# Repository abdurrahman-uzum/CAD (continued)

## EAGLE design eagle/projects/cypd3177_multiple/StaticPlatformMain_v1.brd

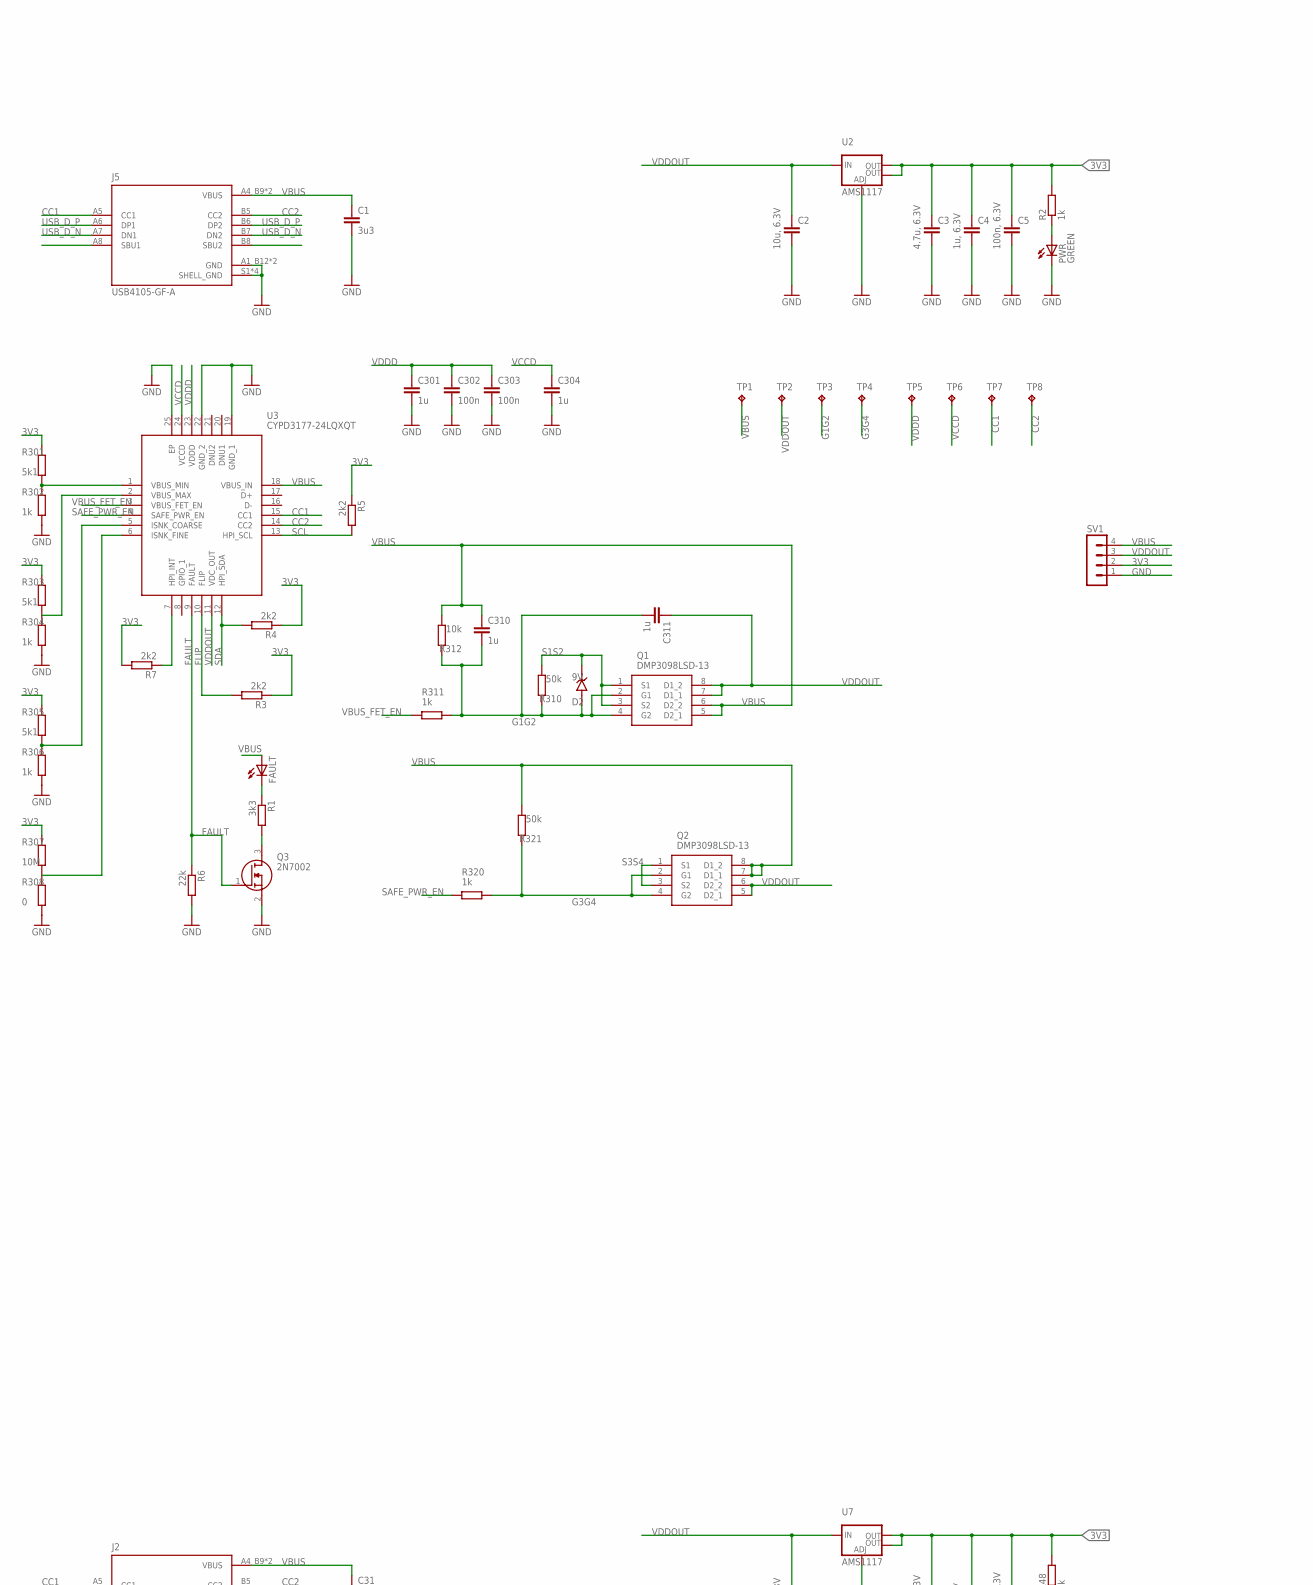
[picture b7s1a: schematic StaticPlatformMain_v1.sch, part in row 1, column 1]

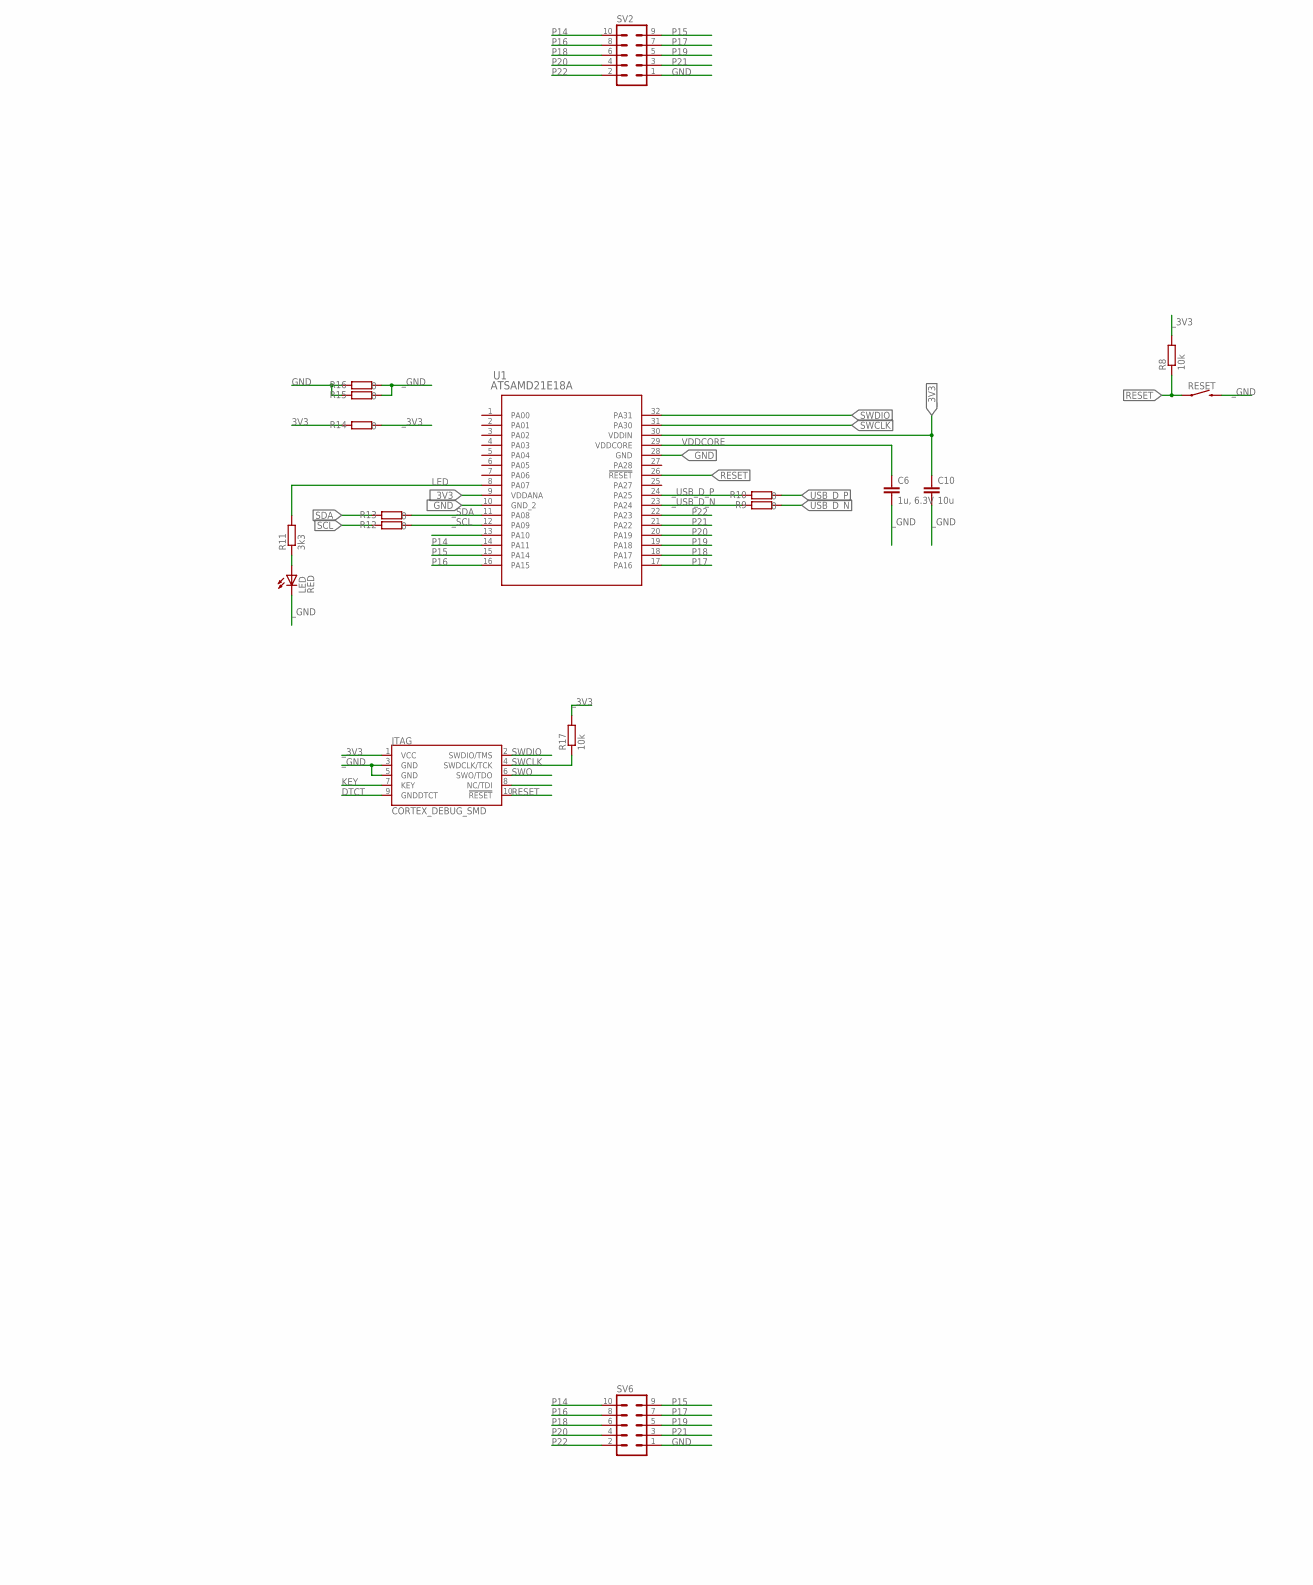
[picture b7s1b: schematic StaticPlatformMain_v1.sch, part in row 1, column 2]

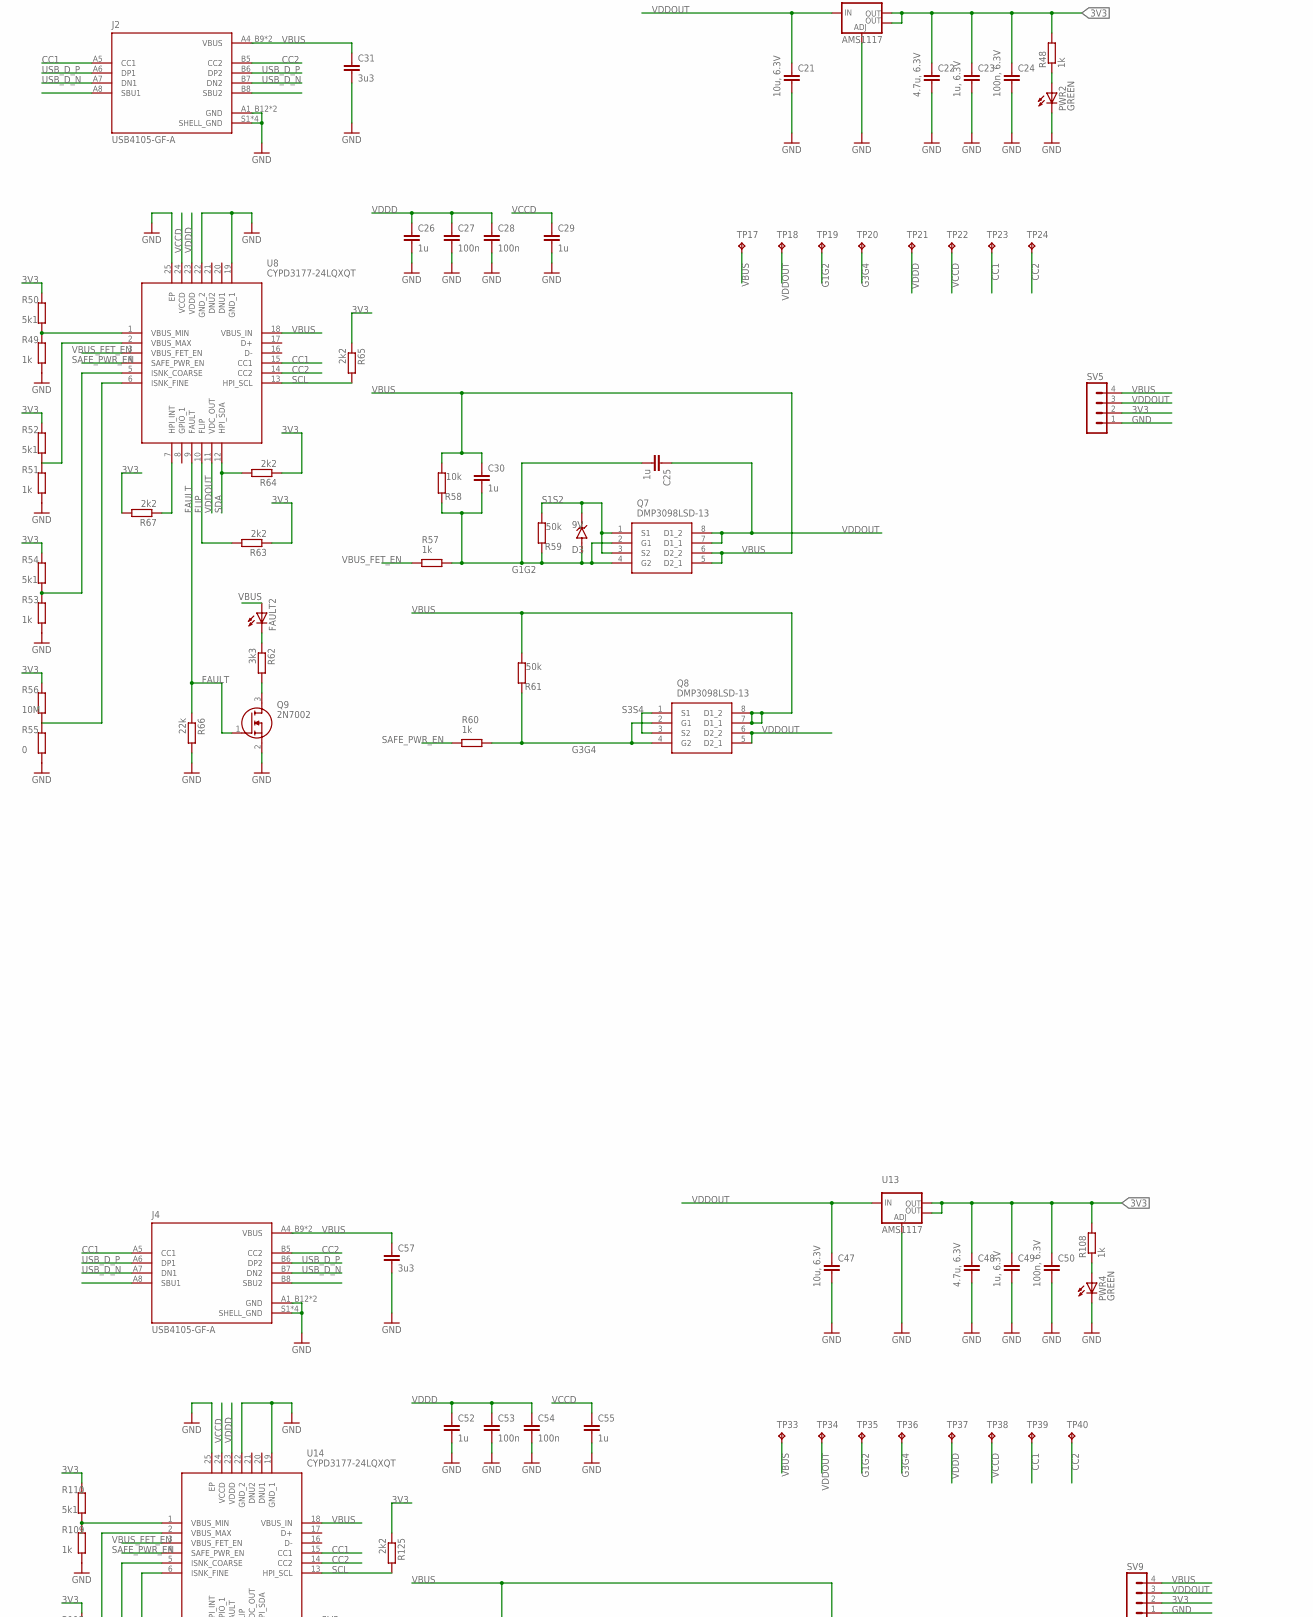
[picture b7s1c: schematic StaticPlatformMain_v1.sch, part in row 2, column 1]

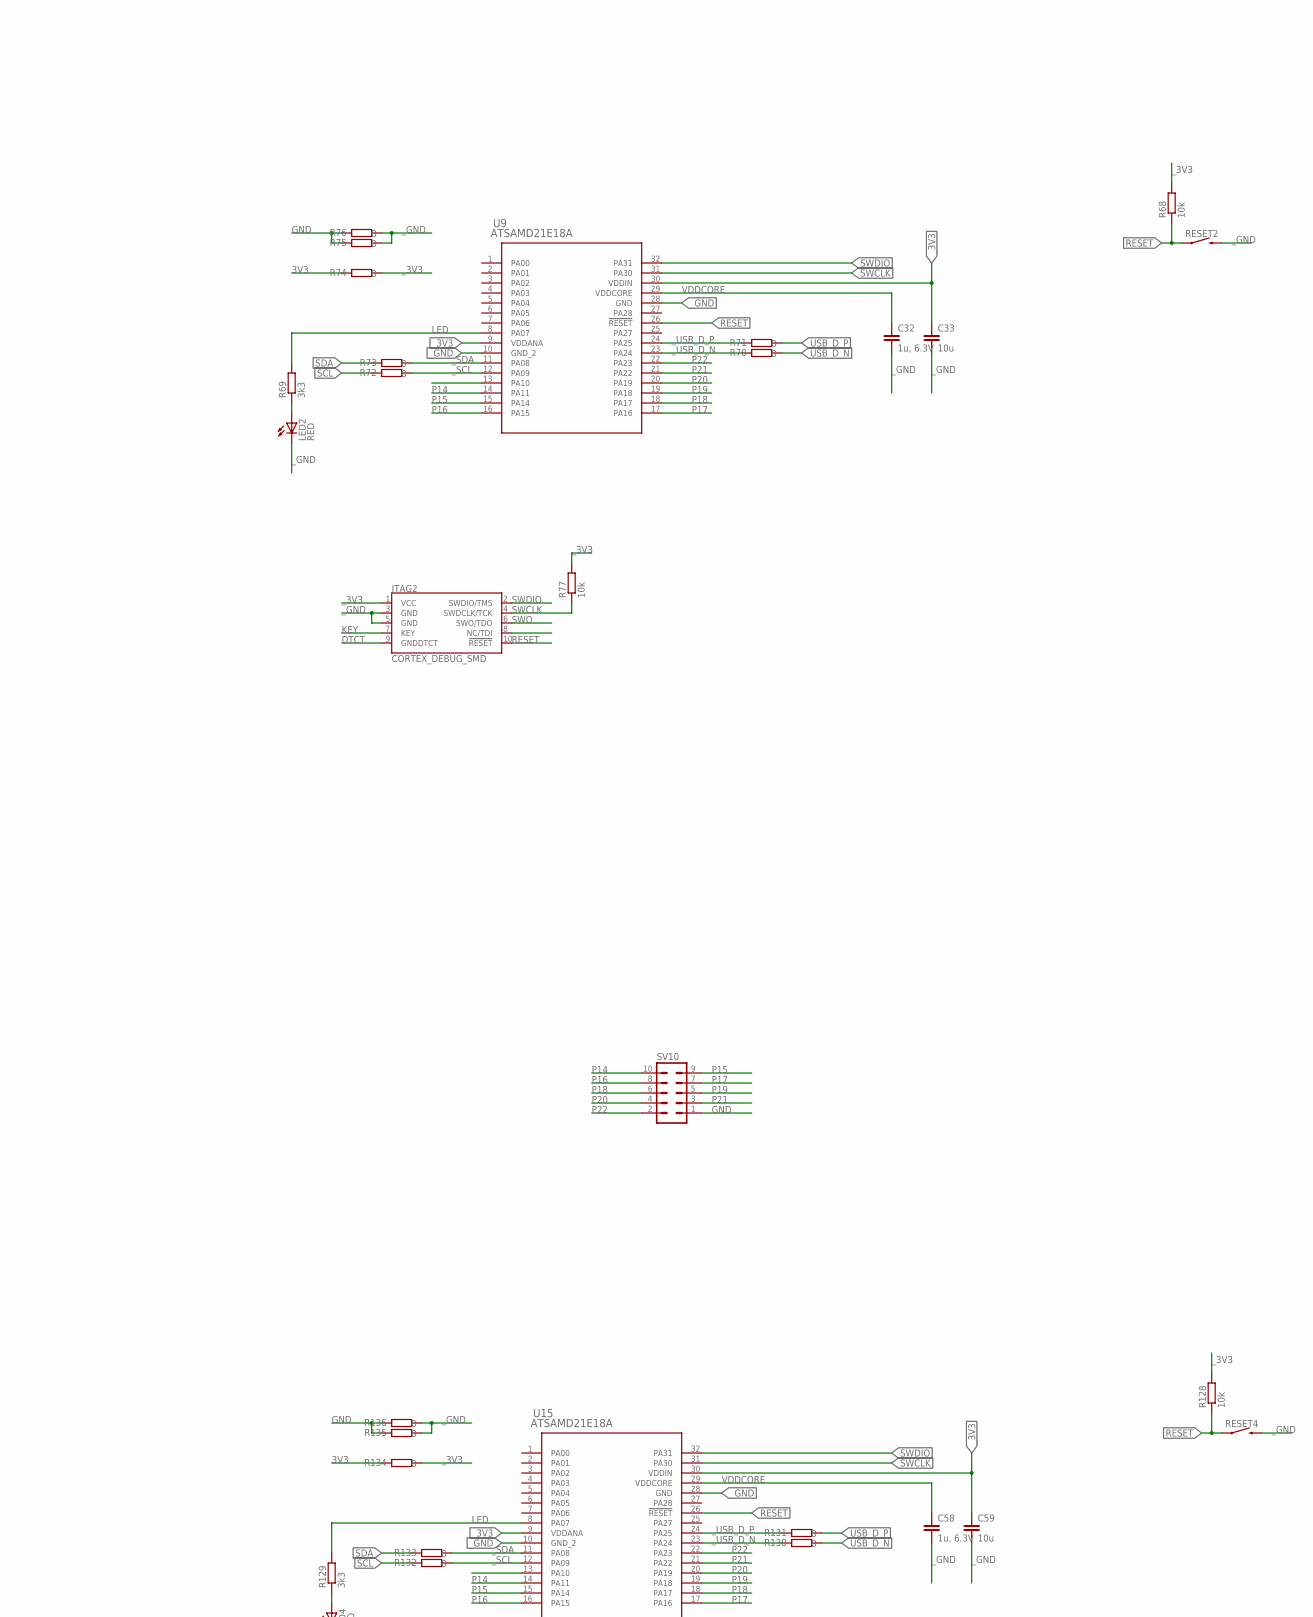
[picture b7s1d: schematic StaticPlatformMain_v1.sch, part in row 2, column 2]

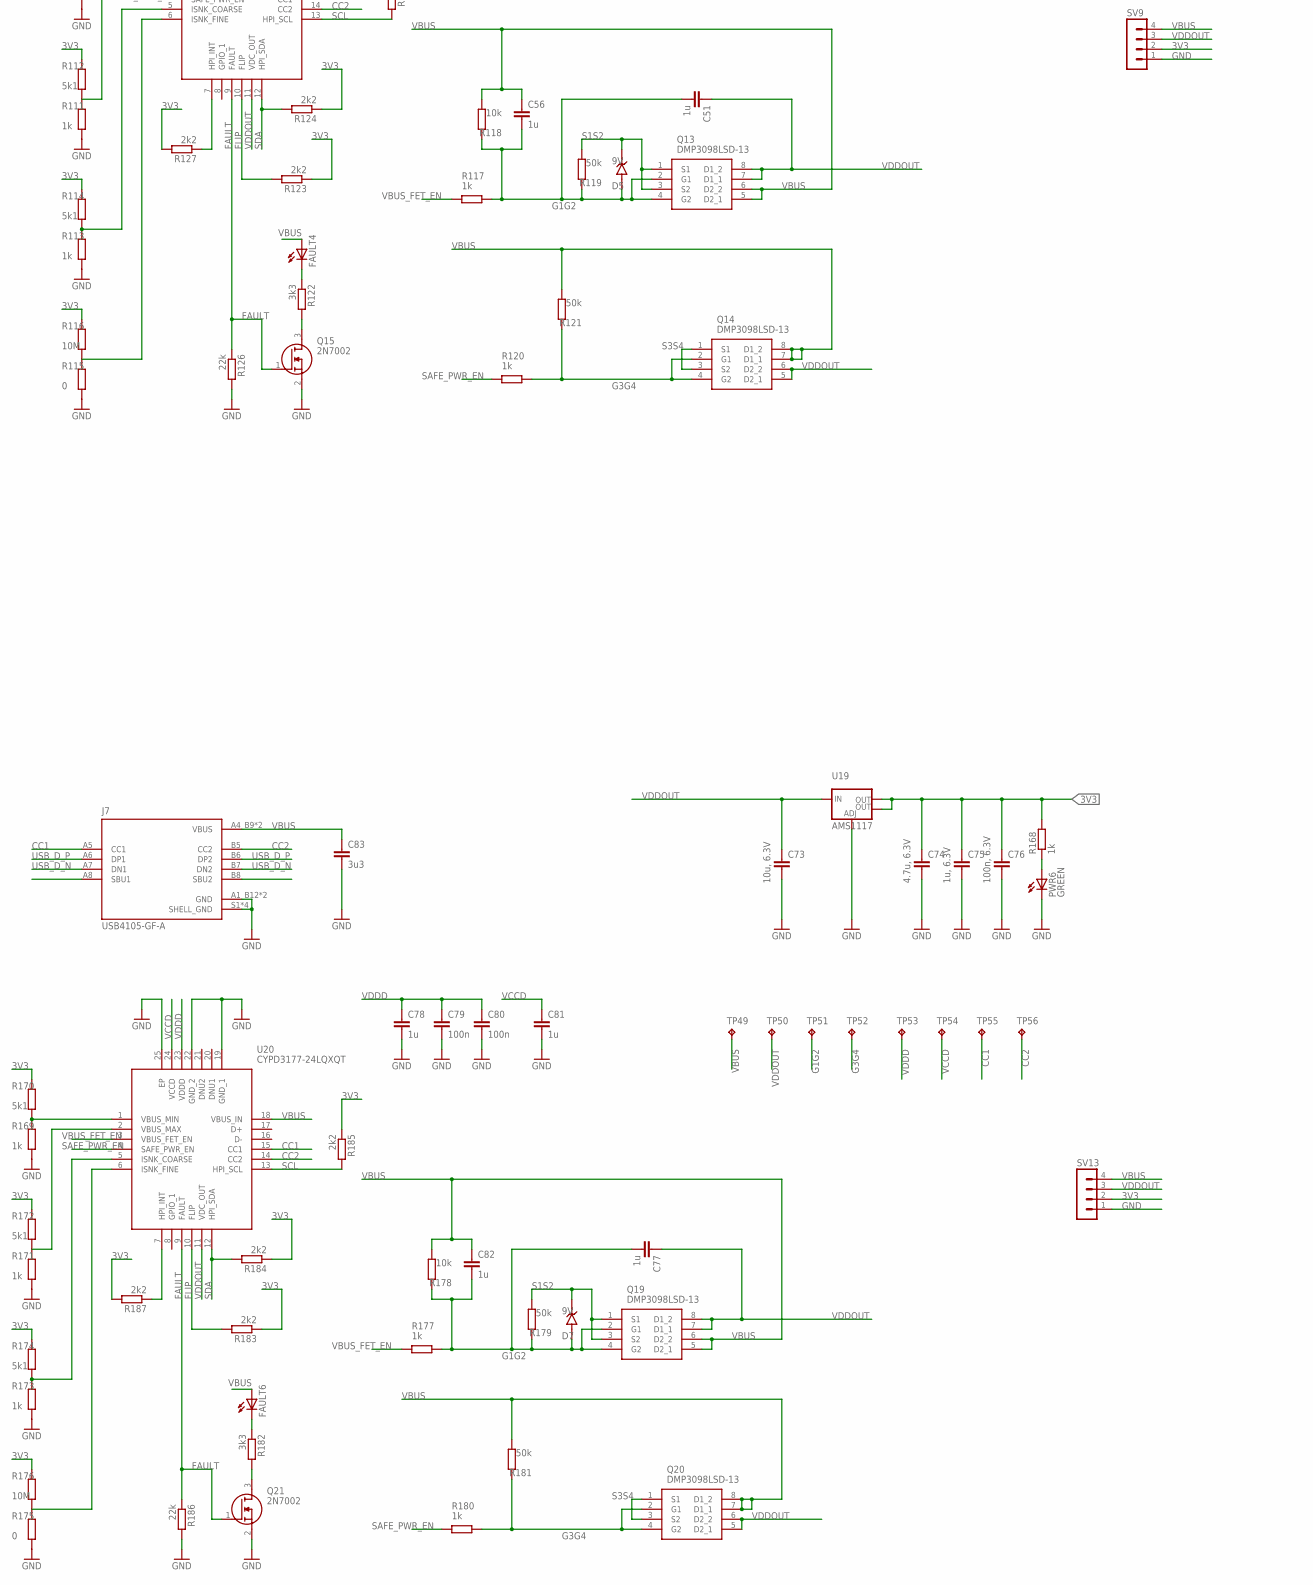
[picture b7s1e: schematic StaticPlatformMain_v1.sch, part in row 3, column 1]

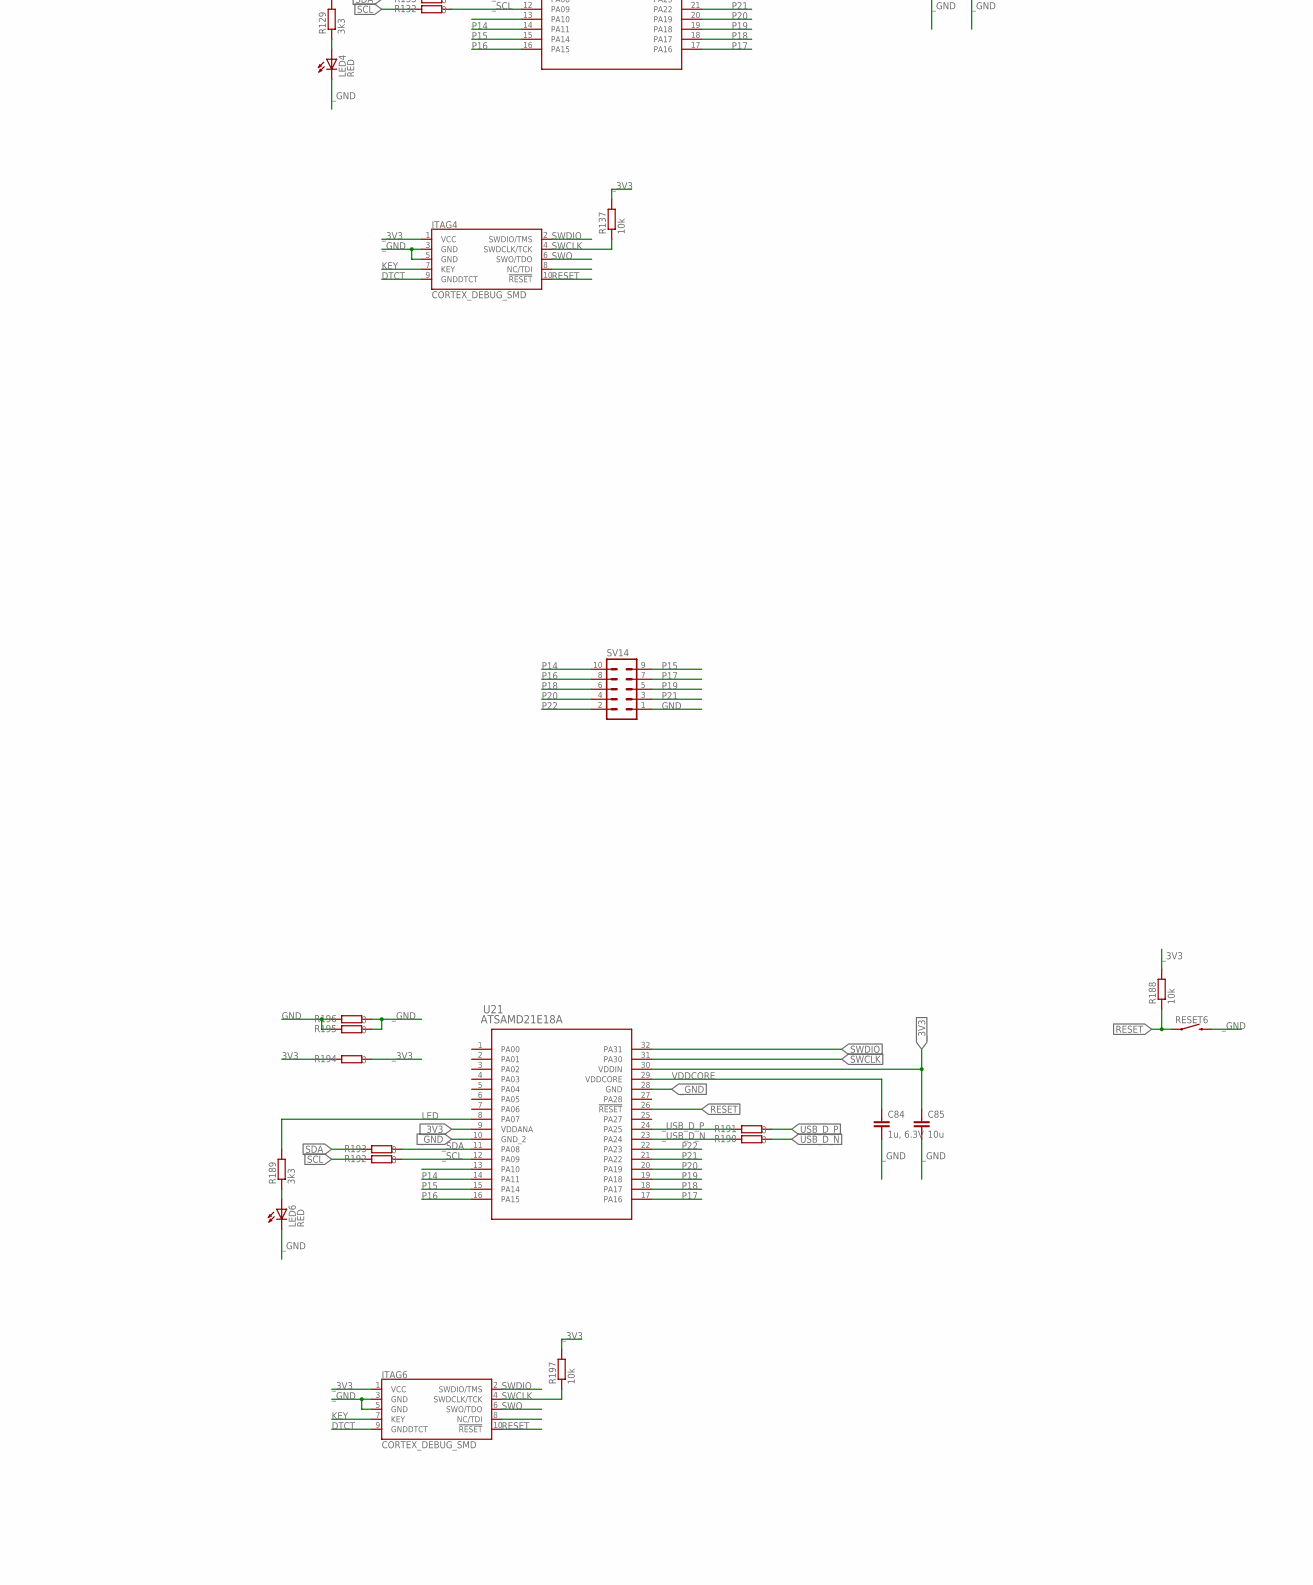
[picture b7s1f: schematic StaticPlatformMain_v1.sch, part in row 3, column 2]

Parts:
C1, C31, C57, C83: 3u3; C0805K
C2, C21, C47, C73: 10u, 6.3V; C0805K
C3, C22, C48, C74: 4.7u, 6.3V; C0805K
C4, C23, C49, C75: 1u, 6.3V; C0805K
C5, C24, C50, C76: 100n, 6.3V; C0805K
C6, C32, C58, C84: 1u, 6.3V; C0805
C10, C33, C59, C85: 10u; C0805
C25, C26, C29, C30, C51, C52, C55, C56, C77, C78, C81, C82, C301, C304, C310, C311: 1u; C0805K
C27, C28, C53, C54, C79, C80, C302, C303: 100n; C0805K
D2, D3, D5, D7: 9V; DIOMELF3515N
FAULT, FAULT2, FAULT4, FAULT6: GREEN; CHIPLED_0805
J2, J4, J5, J7: USB4105-GF-A; GCT_USB4105-GF-A
JTAG, JTAG2, JTAG4, JTAG6: CORTEX_DEBUG_SMD; SAMTECH_FTSH-105-01
LED, LED2, LED4, LED6: RED; CHIPLED_0805
PWR, PWR2, PWR4, PWR6: GREEN; CHIPLED_0805
Q1, Q2, Q7, Q8, Q13, Q14, Q19, Q20: DMP3098LSD-13; SOIC127P600X175-8N
Q3, Q9, Q15, Q21: 2N7002; SOT96P240X120-3N
R1, R11, R62, R69, R122, R129, R182, R189: 3k3; R0805
R2, R48, R49, R51, R53, R57, R60, R108, R109, R111, R113, R117, R120, R168, R169, R171, R173, R177, R180, R302, R304, R306, R311, R320: 1k; R0805
R3, R4, R5, R7, R63, R64, R65, R67, R123, R124, R125, R127, R183, R184, R185, R187: 2k2; R0805
R6, R66, R126, R186: 22k; R0805
R8, R17, R58, R68, R77, R118, R128, R137, R178, R188, R197, R312: 10k; R0805
R9, R10, R12, R13, R14, R15, R16, R55, R70, R71, R72, R73, R74, R75, R76, R115, R130, R131, R132, R133, R134, R135, R136, R175, R190, R191, R192, R193, R194, R195, R196, R308: 0; R0805
R50, R52, R54, R110, R112, R114, R170, R172, R174, R301, R303, R305: 5k1; R0805
R56, R116, R176, R307: 10M; R0805
R59, R61, R119, R121, R179, R181, R310, R321: 50k; R0805
RESET, RESET2, RESET4, RESET6: MOMENTARY-SWITCH-SPST-SMD-6.0X3.5MM; TACTILE_SWITCH_SMD_6.0X3.5MM
SV1, SV5, SV9, SV13: MA04-1
SV2, SV6, SV10, SV14: MA05-2
TP1, TP2, TP3, TP4, TP5, TP6, TP7, TP8, TP17, TP18, TP19, TP20, TP21, TP22, TP23, TP24, TP33, TP34, TP35, TP36, TP37, TP38, TP39, TP40, TP49, TP50, TP51, TP52, TP53, TP54, TP55, TP56: TPTP18R; TP18R
U1, U9, U15, U21: ATSAMD21E18A; TQFP32_MC_MCH-M
U2, U7, U13, U19: AMS1117; SOT223
U3, U8, U14, U20: CYPD3177-24LQXQT; QFN50P400X400X60-25N

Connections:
3V3: C3.1, C4.1, C5.1, C22.1, C23.1, C24.1, C48.1, C49.1, C50.1, C74.1, C75.1, C76.1, R2.2, R3.1, R4.1, R5.1, R7.2, R14.2, R48.2, R50.2, R52.2, R54.2, R56.2, R63.1, R64.1, R65.1, R67.2, R74.2, R108.2, R110.2, R112.2, R114.2, R116.2, R123.1, R124.1, R125.1, R127.2, R134.2, R168.2, R170.2, R172.2, R174.2, R176.2, R183.1, R184.1, R185.1, R187.2, R194.2, R301.2, R303.2, R305.2, R307.2, SV1.2, SV5.2, SV9.2, SV13.2, U2.2 (OUT), U2.4 (OUT), U7.2 (OUT), U7.4 (OUT), U13.2 (OUT), U13.4 (OUT), U19.2 (OUT), U19.4 (OUT)
CC1: J2.A5 (CC1), J4.A5 (CC1), J5.A5 (CC1), J7.A5 (CC1), TP7.TP, TP23.TP, TP39.TP, TP55.TP, U3.15 (CC1), U8.15 (CC1), U14.15 (CC1), U20.15 (CC1)
CC2: J2.B5 (CC2), J4.B5 (CC2), J5.B5 (CC2), J7.B5 (CC2), TP8.TP, TP24.TP, TP40.TP, TP56.TP, U3.14 (CC2), U8.14 (CC2), U14.14 (CC2), U20.14 (CC2)
DTCT: JTAG.9 (GNDDTCT), JTAG2.9 (GNDDTCT), JTAG4.9 (GNDDTCT), JTAG6.9 (GNDDTCT)
FAULT: Q3.1 (G), Q9.1 (G), Q15.1 (G), Q21.1 (G), R6.1, R66.1, R126.1, R186.1, U3.9 (FAULT), U8.9 (FAULT), U14.9 (FAULT), U20.9 (FAULT)
FLIP: R3.2, R63.2, R123.2, R183.2, U3.10 (FLIP), U8.10 (FLIP), U14.10 (FLIP), U20.10 (FLIP)
G1G2: C25.2, C30.2, C51.2, C56.2, C77.2, C82.2, C310.2, C311.2, D2.A, D3.A, D5.A, D7.A, Q1.2 (G1), Q1.4 (G2), Q7.2 (G1), Q7.4 (G2), Q13.2 (G1), Q13.4 (G2), Q19.2 (G1), Q19.4 (G2), R57.1, R58.2, R59.2, R117.1, R118.2, R119.2, R177.1, R178.2, R179.2, R310.2, R311.1, R312.2, TP3.TP, TP19.TP, TP35.TP, TP51.TP
G3G4: Q2.2 (G1), Q2.4 (G2), Q8.2 (G1), Q8.4 (G2), Q14.2 (G1), Q14.4 (G2), Q20.2 (G1), Q20.4 (G2), R60.1, R61.2, R120.1, R121.2, R180.1, R181.2, R320.1, R321.2, TP4.TP, TP20.TP, TP36.TP, TP52.TP
GND: C1.2, C2.2, C3.2, C4.2, C5.2, C21.2, C22.2, C23.2, C24.2, C26.2, C27.2, C28.2, C29.2, C31.2, C47.2, C48.2, C49.2, C50.2, C52.2, C53.2, C54.2, C55.2, C57.2, C73.2, C74.2, C75.2, C76.2, C78.2, C79.2, C80.2, C81.2, C83.2, C301.2, C302.2, C303.2, C304.2, J2.A1_B12 (GND), J2.B1_A12 (GND), J2.S1 (SHELL_GND), J2.S2 (SHELL_GND), J2.S3 (SHELL_GND), J2.S4 (SHELL_GND), J4.A1_B12 (GND), J4.B1_A12 (GND), J4.S1 (SHELL_GND), J4.S2 (SHELL_GND), J4.S3 (SHELL_GND), J4.S4 (SHELL_GND), J5.A1_B12 (GND), J5.B1_A12 (GND), J5.S1 (SHELL_GND), J5.S2 (SHELL_GND), J5.S3 (SHELL_GND), J5.S4 (SHELL_GND), J7.A1_B12 (GND), J7.B1_A12 (GND), J7.S1 (SHELL_GND), J7.S2 (SHELL_GND), J7.S3 (SHELL_GND), J7.S4 (SHELL_GND), PWR.C, PWR2.C, PWR4.C, PWR6.C, Q3.2 (S), Q9.2 (S), Q15.2 (S), Q21.2 (S), R6.2, R15.2, R16.2, R49.1, R51.1, R53.1, R55.1, R66.2, R75.2, R76.2, R109.1, R111.1, R113.1, R115.1, R126.2, R135.2, R136.2, R169.1, R171.1, R173.1, R175.1, R186.2, R195.2, R196.2, R302.1, R304.1, R306.1, R308.1, SV1.1, SV2.1, SV5.1, SV6.1, SV9.1, SV10.1, SV13.1, SV14.1, U2.1 (ADJ), U3.19 (GND_1), U3.22 (GND_2), U3.25 (EP), U7.1 (ADJ), U8.19 (GND_1), U8.22 (GND_2), U8.25 (EP), U13.1 (ADJ), U14.19 (GND_1), U14.22 (GND_2), U14.25 (EP), U19.1 (ADJ), U20.19 (GND_1), U20.22 (GND_2), U20.25 (EP)
KEY: JTAG.7 (KEY), JTAG2.7 (KEY), JTAG4.7 (KEY), JTAG6.7 (KEY)
LED: R11.2, R69.2, R129.2, R189.2, U1.8 (PA07), U9.8 (PA07), U15.8 (PA07), U21.8 (PA07)
LED_GP: LED.A, R11.1
LED_GP2: LED2.A, R69.1
LED_GP4: LED4.A, R129.1
LED_GP6: LED6.A, R189.1
LED_PWR: PWR.A, R2.1
LED_PWR2: PWR2.A, R48.1
LED_PWR4: PWR4.A, R108.1
LED_PWR6: PWR6.A, R168.1
unnamed: FAULT.C, R1.1
unnamed: R7.1, U3.7 (HPI_INT)
unnamed: R301.1, R302.2, U3.1 (VBUS_MIN)
unnamed: R303.1, R304.2, U3.2 (VBUS_MAX)
unnamed: R305.1, R306.2, U3.5 (ISNK_COARSE)
unnamed: Q3.3 (D), R1.2
unnamed: R307.1, R308.2, U3.6 (ISNK_FINE)
unnamed: R49.2, R50.1, U8.1 (VBUS_MIN)
unnamed: R51.2, R52.1, U8.2 (VBUS_MAX)
unnamed: R53.2, R54.1, U8.5 (ISNK_COARSE)
unnamed: R55.2, R56.1, U8.6 (ISNK_FINE)
unnamed: FAULT2.C, R62.1
unnamed: Q9.3 (D), R62.2
unnamed: R67.1, U8.7 (HPI_INT)
unnamed: R109.2, R110.1, U14.1 (VBUS_MIN)
unnamed: R111.2, R112.1, U14.2 (VBUS_MAX)
unnamed: R113.2, R114.1, U14.5 (ISNK_COARSE)
unnamed: R115.2, R116.1, U14.6 (ISNK_FINE)
unnamed: FAULT4.C, R122.1
unnamed: Q15.3 (D), R122.2
unnamed: R127.1, U14.7 (HPI_INT)
unnamed: R169.2, R170.1, U20.1 (VBUS_MIN)
unnamed: R171.2, R172.1, U20.2 (VBUS_MAX)
unnamed: R173.2, R174.1, U20.5 (ISNK_COARSE)
unnamed: R175.2, R176.1, U20.6 (ISNK_FINE)
unnamed: FAULT6.C, R182.1
unnamed: Q21.3 (D), R182.2
unnamed: R187.1, U20.7 (HPI_INT)
P14: SV2.10, SV6.10, SV10.10, SV14.10, U1.14 (PA11), U9.14 (PA11), U15.14 (PA11), U21.14 (PA11)
P15: SV2.9, SV6.9, SV10.9, SV14.9, U1.15 (PA14), U9.15 (PA14), U15.15 (PA14), U21.15 (PA14)
P16: SV2.8, SV6.8, SV10.8, SV14.8, U1.16 (PA15), U9.16 (PA15), U15.16 (PA15), U21.16 (PA15)
P17: SV2.7, SV6.7, SV10.7, SV14.7, U1.17 (PA16), U9.17 (PA16), U15.17 (PA16), U21.17 (PA16)
P18: SV2.6, SV6.6, SV10.6, SV14.6, U1.18 (PA17), U9.18 (PA17), U15.18 (PA17), U21.18 (PA17)
P19: SV2.5, SV6.5, SV10.5, SV14.5, U1.19 (PA18), U9.19 (PA18), U15.19 (PA18), U21.19 (PA18)
P20: SV2.4, SV6.4, SV10.4, SV14.4, U1.20 (PA19), U9.20 (PA19), U15.20 (PA19), U21.20 (PA19)
P21: SV2.3, SV6.3, SV10.3, SV14.3, U1.21 (PA22), U9.21 (PA22), U15.21 (PA22), U21.21 (PA22)
P22: SV2.2, SV6.2, SV10.2, SV14.2, U1.22 (PA23), U9.22 (PA23), U15.22 (PA23), U21.22 (PA23)
RESET: JTAG.10 (!RESET), JTAG2.10 (!RESET), JTAG4.10 (!RESET), JTAG6.10 (!RESET), R8.1, R68.1, R128.1, R188.1, RESET.1, RESET2.1, RESET4.1, RESET6.1, U1.26 (!RESET), U9.26 (!RESET), U15.26 (!RESET), U21.26 (!RESET)
S1S2: D2.C (K), D3.C (K), D5.C (K), D7.C (K), Q1.1 (S1), Q1.3 (S2), Q7.1 (S1), Q7.3 (S2), Q13.1 (S1), Q13.3 (S2), Q19.1 (S1), Q19.3 (S2), R59.1, R119.1, R179.1, R310.1
S3S4: Q2.1 (S1), Q2.3 (S2), Q8.1 (S1), Q8.3 (S2), Q14.1 (S1), Q14.3 (S2), Q20.1 (S1), Q20.3 (S2)
SAFE_PWR_EN: R60.2, R120.2, R180.2, R320.2, U3.4 (SAFE_PWR_EN), U8.4 (SAFE_PWR_EN), U14.4 (SAFE_PWR_EN), U20.4 (SAFE_PWR_EN)
SCL: R5.2, R12.2, R65.2, R72.2, R125.2, R132.2, R185.2, R192.2, U3.13 (HPI_SCL), U8.13 (HPI_SCL), U14.13 (HPI_SCL), U20.13 (HPI_SCL)
SDA: R4.2, R13.2, R64.2, R73.2, R124.2, R133.2, R184.2, R193.2, U3.12 (HPI_SDA), U8.12 (HPI_SDA), U14.12 (HPI_SDA), U20.12 (HPI_SDA)
SWCLK: JTAG.4 (SWDCLK/TCK), JTAG2.4 (SWDCLK/TCK), JTAG4.4 (SWDCLK/TCK), JTAG6.4 (SWDCLK/TCK), R17.1, R77.1, R137.1, R197.1, U1.31 (PA30), U9.31 (PA30), U15.31 (PA30), U21.31 (PA30)
SWDIO: JTAG.2 (SWDIO/TMS), JTAG2.2 (SWDIO/TMS), JTAG4.2 (SWDIO/TMS), JTAG6.2 (SWDIO/TMS), U1.32 (PA31), U9.32 (PA31), U15.32 (PA31), U21.32 (PA31)
SWO: JTAG.6 (SWO/TDO), JTAG2.6 (SWO/TDO), JTAG4.6 (SWO/TDO), JTAG6.6 (SWO/TDO)
USB_D_N: J2.A7 (DN1), J2.B7 (DN2), J4.A7 (DN1), J4.B7 (DN2), J5.A7 (DN1), J5.B7 (DN2), J7.A7 (DN1), J7.B7 (DN2), R9.1, R70.1, R130.1, R190.1
USB_D_P: J2.A6 (DP1), J2.B6 (DP2), J4.A6 (DP1), J4.B6 (DP2), J5.A6 (DP1), J5.B6 (DP2), J7.A6 (DP1), J7.B6 (DP2), R10.1, R71.1, R131.1, R191.1
VBUS: C1.1, C30.1, C31.1, C56.1, C57.1, C82.1, C83.1, C310.1, FAULT.A, FAULT2.A, FAULT4.A, FAULT6.A, J2.A4_B9 (VBUS), J2.B4_A9 (VBUS), J4.A4_B9 (VBUS), J4.B4_A9 (VBUS), J5.A4_B9 (VBUS), J5.B4_A9 (VBUS), J7.A4_B9 (VBUS), J7.B4_A9 (VBUS), Q1.5 (D2_1), Q1.6 (D2_2), Q2.7 (D1_1), Q2.8 (D1_2), Q7.5 (D2_1), Q7.6 (D2_2), Q8.7 (D1_1), Q8.8 (D1_2), Q13.5 (D2_1), Q13.6 (D2_2), Q14.7 (D1_1), Q14.8 (D1_2), Q19.5 (D2_1), Q19.6 (D2_2), Q20.7 (D1_1), Q20.8 (D1_2), R58.1, R61.1, R118.1, R121.1, R178.1, R181.1, R312.1, R321.1, SV1.4, SV5.4, SV9.4, SV13.4, TP1.TP, TP17.TP, TP33.TP, TP49.TP, U3.18 (VBUS_IN), U8.18 (VBUS_IN), U14.18 (VBUS_IN), U20.18 (VBUS_IN)
VBUS_FET_EN: R57.2, R117.2, R177.2, R311.2, U3.3 (VBUS_FET_EN), U8.3 (VBUS_FET_EN), U14.3 (VBUS_FET_EN), U20.3 (VBUS_FET_EN)
VCCD: C29.1, C55.1, C81.1, C304.1, TP6.TP, TP22.TP, TP38.TP, TP54.TP, U3.24 (VCCD), U8.24 (VCCD), U14.24 (VCCD), U20.24 (VCCD)
VDDCORE: C6.1, C32.1, C58.1, C84.1, U1.29 (VDDCORE), U9.29 (VDDCORE), U15.29 (VDDCORE), U21.29 (VDDCORE)
VDDD: C26.1, C27.1, C28.1, C52.1, C53.1, C54.1, C78.1, C79.1, C80.1, C301.1, C302.1, C303.1, TP5.TP, TP21.TP, TP37.TP, TP53.TP, U3.23 (VDDD), U8.23 (VDDD), U14.23 (VDDD), U20.23 (VDDD)
VDDOUT: C2.1, C21.1, C25.1, C47.1, C51.1, C73.1, C77.1, C311.1, Q1.7 (D1_1), Q1.8 (D1_2), Q2.5 (D2_1), Q2.6 (D2_2), Q7.7 (D1_1), Q7.8 (D1_2), Q8.5 (D2_1), Q8.6 (D2_2), Q13.7 (D1_1), Q13.8 (D1_2), Q14.5 (D2_1), Q14.6 (D2_2), Q19.7 (D1_1), Q19.8 (D1_2), Q20.5 (D2_1), Q20.6 (D2_2), SV1.3, SV5.3, SV9.3, SV13.3, TP2.TP, TP18.TP, TP34.TP, TP50.TP, U2.3 (IN), U3.11 (VDC_OUT), U7.3 (IN), U8.11 (VDC_OUT), U13.3 (IN), U14.11 (VDC_OUT), U19.3 (IN), U20.11 (VDC_OUT)
_3V3: C10.1, C33.1, C59.1, C85.1, JTAG.1 (VCC), JTAG2.1 (VCC), JTAG4.1 (VCC), JTAG6.1 (VCC), R8.2, R14.1, R17.2, R68.2, R74.1, R77.2, R128.2, R134.1, R137.2, R188.2, R194.1, R197.2, U1.9 (VDDANA), U1.30 (VDDIN), U9.9 (VDDANA), U9.30 (VDDIN), U15.9 (VDDANA), U15.30 (VDDIN), U21.9 (VDDANA), U21.30 (VDDIN)
_GND: C6.2, C10.2, C32.2, C33.2, C58.2, C59.2, C84.2, C85.2, JTAG.3 (GND), JTAG.5 (GND), JTAG2.3 (GND), JTAG2.5 (GND), JTAG4.3 (GND), JTAG4.5 (GND), JTAG6.3 (GND), JTAG6.5 (GND), LED.C, LED2.C, LED4.C, LED6.C, R15.1, R16.1, R75.1, R76.1, R135.1, R136.1, R195.1, R196.1, RESET.2, RESET2.2, RESET4.2, RESET6.2, U1.10 (GND_2), U1.28 (GND), U9.10 (GND_2), U9.28 (GND), U15.10 (GND_2), U15.28 (GND), U21.10 (GND_2), U21.28 (GND)
_SCL: R12.1, R72.1, R132.1, R192.1, U1.12 (PA09), U9.12 (PA09), U15.12 (PA09), U21.12 (PA09)
_SDA: R13.1, R73.1, R133.1, R193.1, U1.11 (PA08), U9.11 (PA08), U15.11 (PA08), U21.11 (PA08)
_USB_D_N: R9.2, R70.2, R130.2, R190.2, U1.23 (PA24), U9.23 (PA24), U15.23 (PA24), U21.23 (PA24)
_USB_D_P: R10.2, R71.2, R131.2, R191.2, U1.24 (PA25), U9.24 (PA25), U15.24 (PA25), U21.24 (PA25)

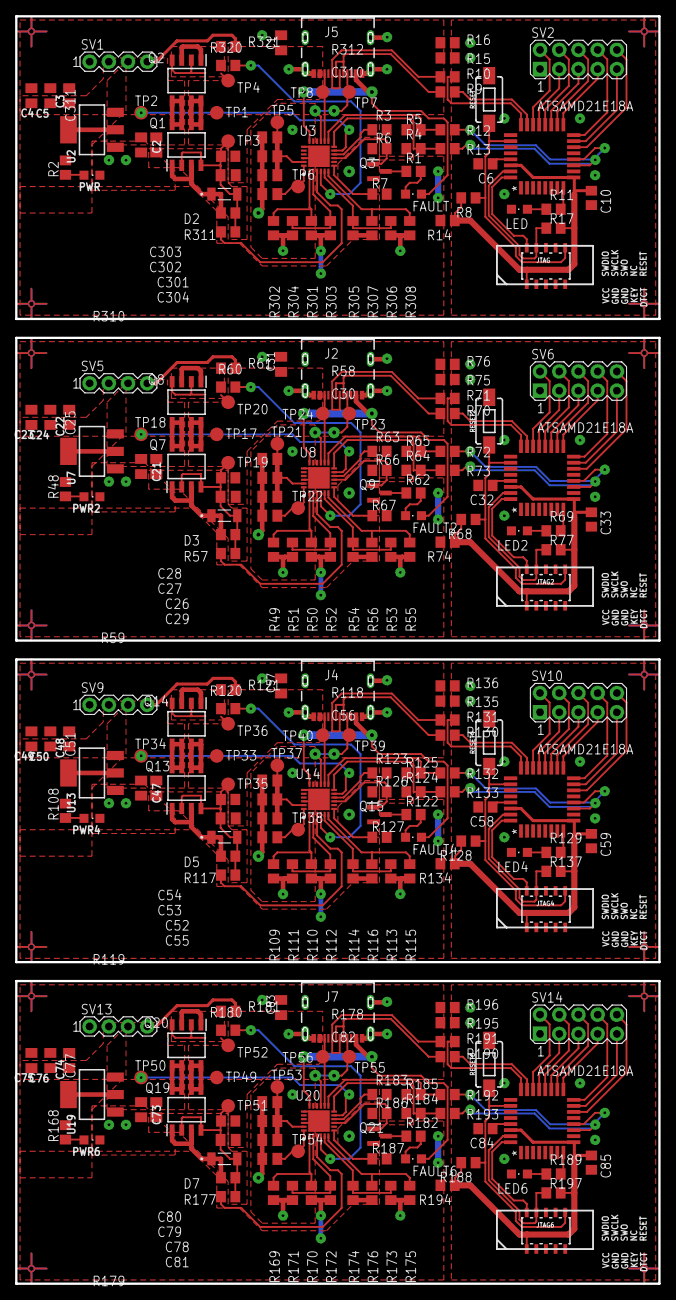
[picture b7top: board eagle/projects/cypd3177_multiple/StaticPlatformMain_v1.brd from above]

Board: 2 copper layers, 85.0 x 167.5 mm, 264 parts (0 on the bottom side), 79 nets.

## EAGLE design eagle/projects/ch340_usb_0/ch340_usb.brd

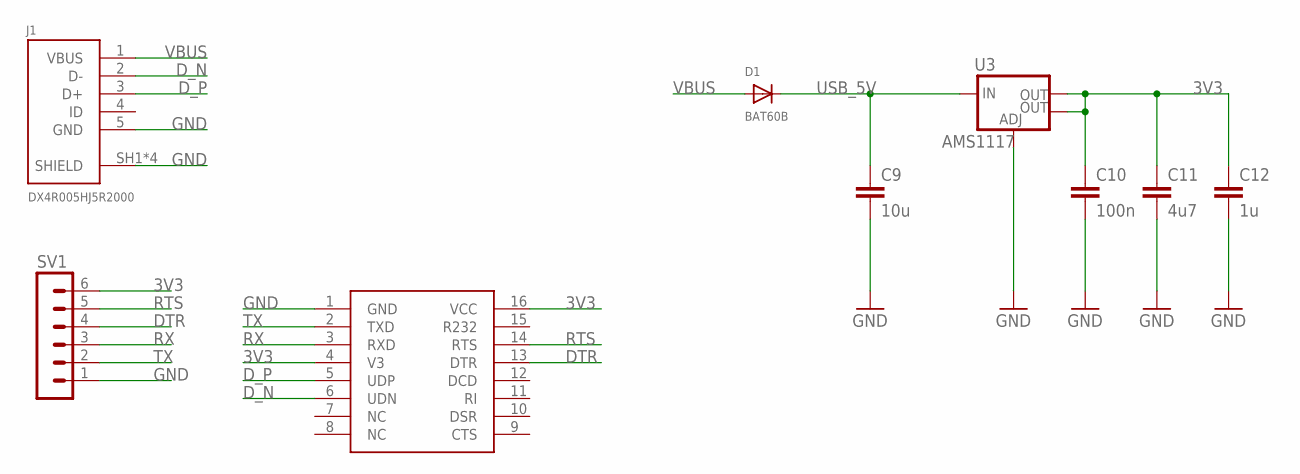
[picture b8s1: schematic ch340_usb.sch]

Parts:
C9: 10u; C0603
C10: 100n; C0603
C11: 4u7; C0603
C12: 1u; C0603
D1: BAT60B; SOD-323F
J1: DX4R005HJ5R2000
SV1: MA06-1
U3: AMS1117; SOT223
U$1: CH340; SOP16

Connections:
3V3: C10.1, C11.1, C12.1, SV1.6, U3.2 (OUT), U3.4 (OUT), U$1.4 (V3), U$1.16 (VCC)
DTR: SV1.4, U$1.13 (DTR)
D_N: J1.2 (D-), U$1.6 (UDN)
D_P: J1.3 (D+), U$1.5 (UDP)
GND: C9.2, C10.2, C11.2, C12.2, J1.5 (GND), J1.SH1 (SHIELD), J1.SH2 (SHIELD), J1.SH3 (SHIELD), J1.SH4 (SHIELD), SV1.1, U3.1 (ADJ), U$1.1 (GND)
RTS: SV1.5, U$1.14 (RTS)
RX: SV1.3, U$1.3 (RXD)
TX: SV1.2, U$1.2 (TXD)
USB_5V: C9.1, D1.C, U3.3 (IN)
VBUS: D1.A, J1.1 (VBUS)

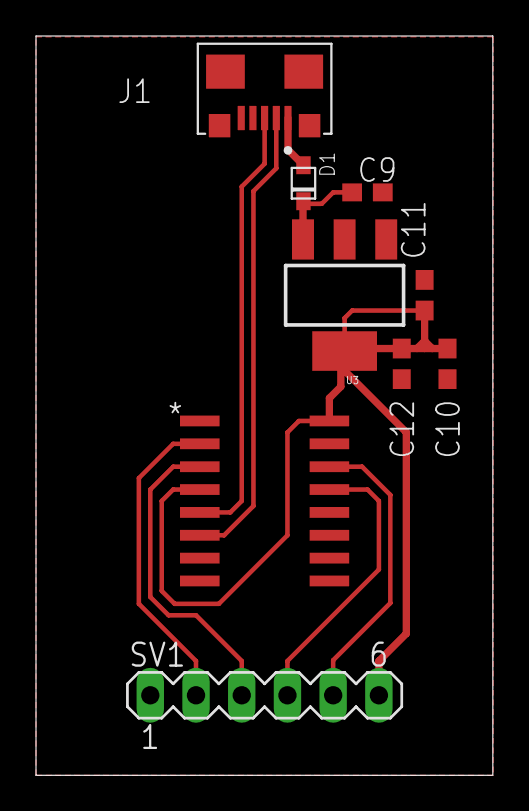
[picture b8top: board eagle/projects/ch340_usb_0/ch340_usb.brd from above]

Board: 2 copper layers, 25.4 x 41.1 mm, 9 parts (0 on the bottom side), 10 nets.

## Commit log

2022-05-16 Backup
2023-03-12 110323
2023-03-27 280323
2024-03-15 150324
2024-05-26 260524
